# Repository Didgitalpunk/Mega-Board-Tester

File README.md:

# Mega-Board-Tester
## An I/O tester made with arduino Uno and arduino mega pinout-compatible boards in mind.
A simple and intuitive microcontroller tester with one LED on each output so you can easiy locate a faulty I/O pin.\
Made for arduino Uno and arduino mega pin-compatible boards (uno, mega, due, leonardo, zero, etc.), but absolutely useable with other boards through jumpers of adapter cables!

https://user-images.githubusercontent.com/29690873/228524618-455ece8d-8ada-4359-9d4d-3bbc245a15be.MOV

## Compatibility
| Board    | State |
|----------|:--:|
| Mega     | 🟢 |
| Leonardo | 🛠️ |
| Uno      | 🟢 |
| Zero     | 🟢 |

## Usage -- using Version 1 board
1. Upload the file MEGA_board_tester__program.ino to your Arduino.
2. Connect the tester to your board.
3. Watch!

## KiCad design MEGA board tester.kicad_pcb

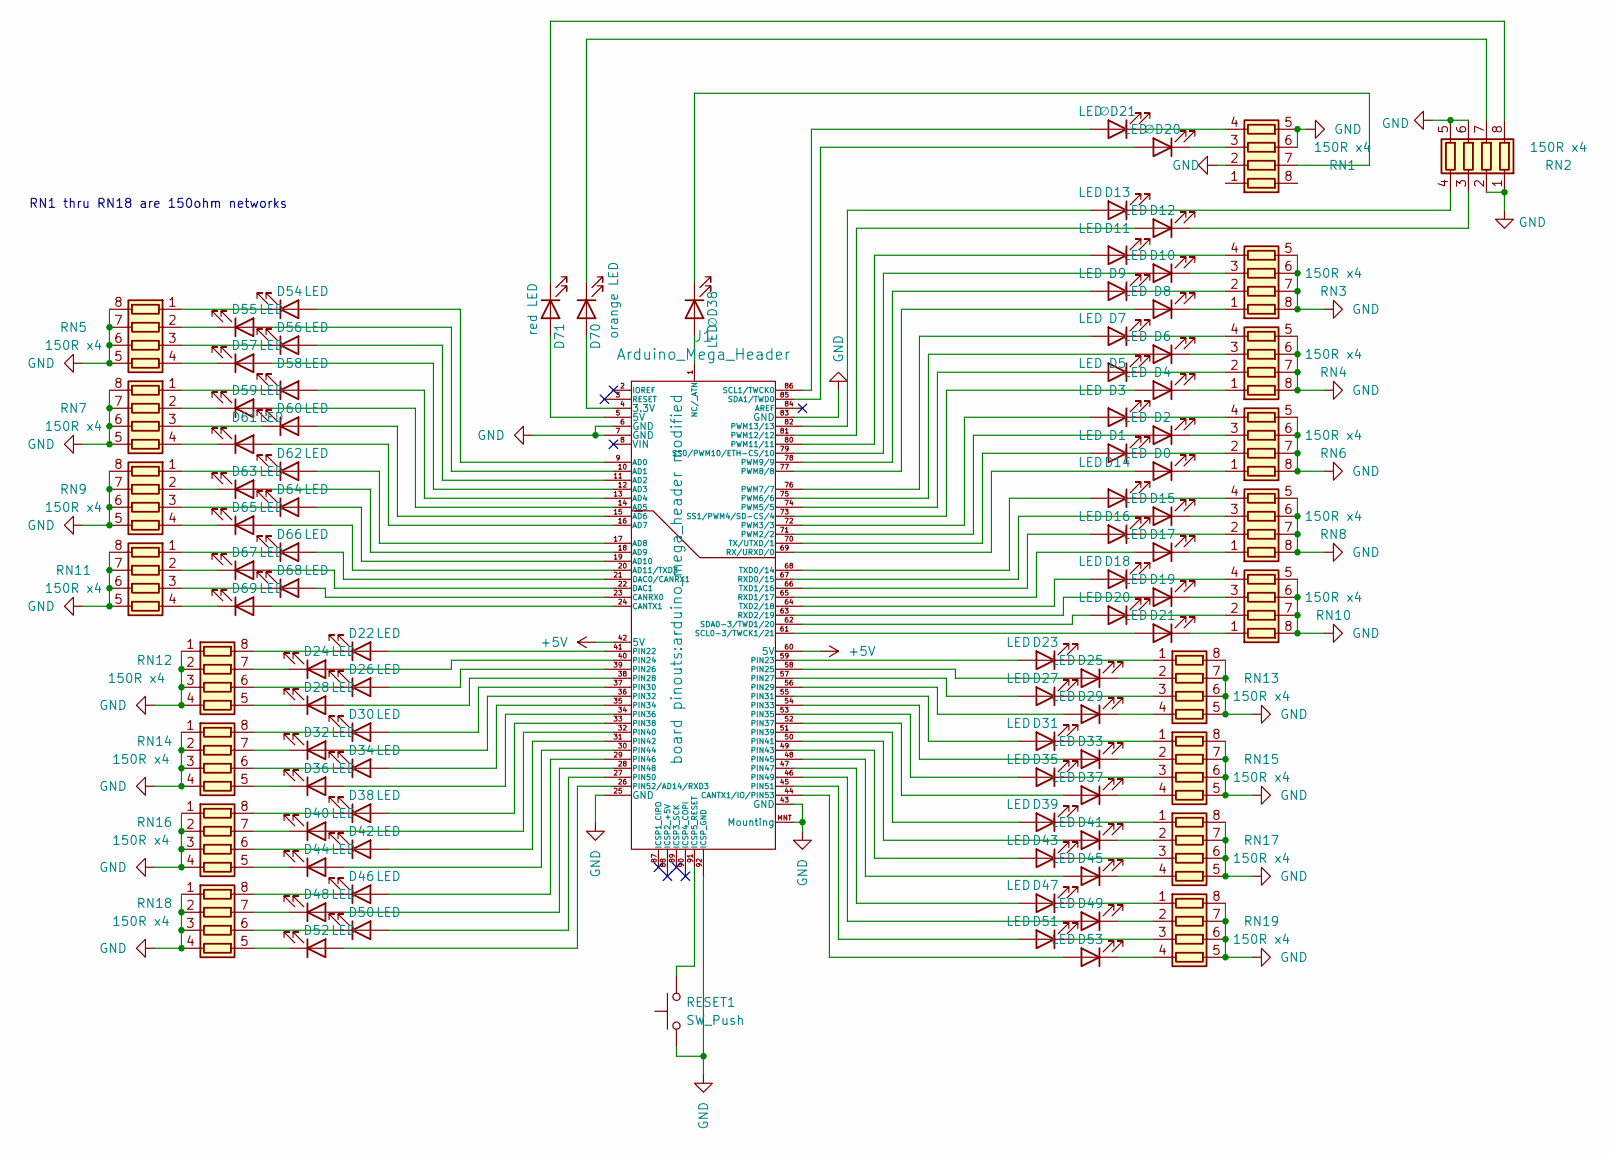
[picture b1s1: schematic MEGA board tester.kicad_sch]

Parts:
D0, D1, D2, D3, D4, D5, D6, D7, D8, D9, D10, D11, D12, D13, D14, D15, D16, D17, D18, D19, D20, D21, D22, D23, D24, D25, D26, D27, D28, D29, D30, D31, D32, D33, D34, D35, D36, D37, D38, D39, D40, D41, D42, D43, D44, D45, D46, D47, D48, D49, D50, D51, D52, D53, D54, D55, D56, D57, D58, D59, D60, D61, D62, D63, D64, D65, D66, D67, D68, D69: LED; D_0805_2012Metric_Pad1.15x1.40mm_HandSolder
D70: orange LED; D_0805_2012Metric_Pad1.15x1.40mm_HandSolder
D71: red LED; D_0805_2012Metric_Pad1.15x1.40mm_HandSolder
J1: Arduino_Mega_Header; arduino_mega_header modified
RESET1: SW_Push; J-lead grayhill switch
RN1, RN2, RN3, RN4, RN5, RN6, RN7, RN8, RN9, RN10, RN11, RN12, RN13, RN14, RN15, RN16, RN17, RN18, RN19: 150R x4; R_Array_convex_EXB-S8Vxxxx
∅D20, ∅D21, ∅D38: LED; D_0805_2012Metric_Pad1.15x1.40mm_HandSolder

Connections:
+5V: J1.42 (5V), J1.60 (5V)
GND: J1.6 (GND), J1.7 (GND), J1.25 (GND), J1.43 (GND), J1.83 (GND), J1.92 (ICSP_GND), J1.MNT (Mounting), RESET1.1, RN1.2 (R2.1), RN1.5 (R4.2), RN1.6 (R3.2), RN2.1 (R1.1), RN2.2 (R2.1), RN2.5 (R4.2), RN2.6 (R3.2), RN3.5 (R4.2), RN3.6 (R3.2), RN3.7 (R2.2), RN3.8 (R1.2), RN4.5 (R4.2), RN4.6 (R3.2), RN4.7 (R2.2), RN4.8 (R1.2), RN5.5 (R4.2), RN5.6 (R3.2), RN5.7 (R2.2), RN5.8 (R1.2), RN6.5 (R4.2), RN6.6 (R3.2), RN6.7 (R2.2), RN6.8 (R1.2), RN7.5 (R4.2), RN7.6 (R3.2), RN7.7 (R2.2), RN7.8 (R1.2), RN8.5 (R4.2), RN8.6 (R3.2), RN8.7 (R2.2), RN8.8 (R1.2), RN9.5 (R4.2), RN9.6 (R3.2), RN9.7 (R2.2), RN9.8 (R1.2), RN10.5 (R4.2), RN10.6 (R3.2), RN10.7 (R2.2), RN10.8 (R1.2), RN11.5 (R4.2), RN11.6 (R3.2), RN11.7 (R2.2), RN11.8 (R1.2), RN12.1 (R1.1), RN12.2 (R2.1), RN12.3 (R3.1), RN12.4 (R4.1), RN13.5 (R4.2), RN13.6 (R3.2), RN13.7 (R2.2), RN13.8 (R1.2), RN14.1 (R1.1), RN14.2 (R2.1), RN14.3 (R3.1), RN14.4 (R4.1), RN15.5 (R4.2), RN15.6 (R3.2), RN15.7 (R2.2), RN15.8 (R1.2), RN16.1 (R1.1), RN16.2 (R2.1), RN16.3 (R3.1), RN16.4 (R4.1), RN17.5 (R4.2), RN17.6 (R3.2), RN17.7 (R2.2), RN17.8 (R1.2), RN18.1 (R1.1), RN18.2 (R2.1), RN18.3 (R3.1), RN18.4 (R4.1), RN19.5 (R4.2), RN19.6 (R3.2), RN19.7 (R2.2), RN19.8 (R1.2); also elsewhere on the board
unnamed: D0.1 (K), RN6.1 (R1.1)
unnamed: D0.2 (A), J1.69 (RX/URXD/0)
unnamed: D1.1 (K), RN6.2 (R2.1)
unnamed: D1.2 (A), J1.70 (TX/UTXD/1)
unnamed: D2.1 (K), RN6.3 (R3.1)
unnamed: D2.2 (A), J1.71 (PWM2/2)
unnamed: D3.1 (K), RN6.4 (R4.1)
unnamed: D3.2 (A), J1.72 (PWM3/3)
unnamed: D4.1 (K), RN4.1 (R1.1)
unnamed: D4.2 (A), J1.73 (SS1/PWM4/SD-CS/4)
unnamed: D5.1 (K), RN4.2 (R2.1)
unnamed: D5.2 (A), J1.74 (PWM5/5)
unnamed: D6.1 (K), RN4.3 (R3.1)
unnamed: D6.2 (A), J1.75 (PWM6/6)
unnamed: D7.1 (K), RN4.4 (R4.1)
unnamed: D7.2 (A), J1.76 (PWM7/7)
unnamed: D8.1 (K), RN3.1 (R1.1)
unnamed: D8.2 (A), J1.77 (PWM8/8)
unnamed: D9.1 (K), RN3.2 (R2.1)
unnamed: D9.2 (A), J1.78 (PWM9/9)
unnamed: D10.1 (K), RN3.3 (R3.1)
unnamed: D10.2 (A), J1.79 (SS0/PWM10/ETH-CS/10)
unnamed: D11.1 (K), RN3.4 (R4.1)
unnamed: D11.2 (A), J1.80 (PWM11/11)
unnamed: D12.1 (K), RN2.3 (R3.1)
unnamed: D12.2 (A), J1.81 (PWM12/12)
unnamed: D13.1 (K), RN2.4 (R4.1)
unnamed: D13.2 (A), J1.82 (PWM13/13)
unnamed: D14.1 (K), RN8.4 (R4.1)
unnamed: D14.2 (A), J1.68 (TXD0/14)
unnamed: D15.1 (K), RN8.3 (R3.1)
unnamed: D15.2 (A), J1.67 (RXD0/15)
unnamed: D16.1 (K), RN8.2 (R2.1)
unnamed: D16.2 (A), J1.66 (TXD1/16)
unnamed: D17.1 (K), RN8.1 (R1.1)
unnamed: D17.2 (A), J1.65 (RXD1/17)
unnamed: D18.1 (K), RN10.4 (R4.1)
unnamed: D18.2 (A), J1.64 (TXD2/18)
unnamed: D19.1 (K), RN10.3 (R3.1)
unnamed: D19.2 (A), J1.63 (RXD2/19)
unnamed: D20.1 (K), RN10.2 (R2.1)
unnamed: D20.2 (A), J1.62 (SDA0-3/TWD1/20)
unnamed: D21.1 (K), RN10.1 (R1.1)
unnamed: D21.2 (A), J1.61 (SCL0-3/TWCK1/21)
unnamed: D22.1 (K), RN12.8 (R1.2)
unnamed: D22.2 (A), J1.41 (PIN22)
unnamed: D23.1 (K), RN13.1 (R1.1)
unnamed: D23.2 (A), J1.59 (PIN23)
unnamed: D24.1 (K), RN12.7 (R2.2)
unnamed: D24.2 (A), J1.40 (PIN24)
unnamed: D25.1 (K), RN13.2 (R2.1)
unnamed: D25.2 (A), J1.58 (PIN25)
unnamed: D26.1 (K), RN12.6 (R3.2)
unnamed: D26.2 (A), J1.39 (PIN26)
unnamed: D27.1 (K), RN13.3 (R3.1)
unnamed: D27.2 (A), J1.57 (PIN27)
unnamed: D28.1 (K), RN12.5 (R4.2)
unnamed: D28.2 (A), J1.38 (PIN28)
unnamed: D29.1 (K), RN13.4 (R4.1)
unnamed: D29.2 (A), J1.56 (PIN29)
unnamed: D30.1 (K), RN14.8 (R1.2)
unnamed: D30.2 (A), J1.37 (PIN30)
unnamed: D31.1 (K), RN15.1 (R1.1)
unnamed: D31.2 (A), J1.55 (PIN31)
unnamed: D32.1 (K), RN14.7 (R2.2)
unnamed: D32.2 (A), J1.36 (PIN32)
unnamed: D33.1 (K), RN15.2 (R2.1)
unnamed: D33.2 (A), J1.54 (PIN33)
unnamed: D34.1 (K), RN14.6 (R3.2)
unnamed: D34.2 (A), J1.35 (PIN34)
unnamed: D35.1 (K), RN15.3 (R3.1)
unnamed: D35.2 (A), J1.53 (PIN35)
unnamed: D36.1 (K), RN14.5 (R4.2)
unnamed: D36.2 (A), J1.34 (PIN36)
unnamed: D37.1 (K), RN15.4 (R4.1)
unnamed: D37.2 (A), J1.52 (PIN37)
unnamed: D38.1 (K), RN16.8 (R1.2)
unnamed: D38.2 (A), J1.33 (PIN38)
unnamed: D39.1 (K), RN17.1 (R1.1)
unnamed: D39.2 (A), J1.51 (PIN39)
unnamed: D40.1 (K), RN16.7 (R2.2)
unnamed: D40.2 (A), J1.32 (PIN40)
unnamed: D41.1 (K), RN17.2 (R2.1)
unnamed: D41.2 (A), J1.50 (PIN41)
unnamed: D42.1 (K), RN16.6 (R3.2)
unnamed: D42.2 (A), J1.31 (PIN42)
unnamed: D43.1 (K), RN17.3 (R3.1)
unnamed: D43.2 (A), J1.49 (PIN43)
unnamed: D44.1 (K), RN16.5 (R4.2)
unnamed: D44.2 (A), J1.30 (PIN44)
unnamed: D45.1 (K), RN17.4 (R4.1)
unnamed: D45.2 (A), J1.48 (PIN45)
unnamed: D46.1 (K), RN18.8 (R1.2)
unnamed: D46.2 (A), J1.29 (PIN46)
unnamed: D47.1 (K), RN19.1 (R1.1)
unnamed: D47.2 (A), J1.47 (PIN47)
unnamed: D48.1 (K), RN18.7 (R2.2)
unnamed: D48.2 (A), J1.28 (PIN48)
unnamed: D49.1 (K), RN19.2 (R2.1)
unnamed: D49.2 (A), J1.46 (PIN49)
unnamed: D50.1 (K), RN18.6 (R3.2)
unnamed: D50.2 (A), J1.27 (PIN50)
unnamed: D51.1 (K), RN19.3 (R3.1)
unnamed: D51.2 (A), J1.45 (PIN51)
unnamed: D52.1 (K), RN18.5 (R4.2)
unnamed: D52.2 (A), J1.26 (PIN52/AD14/RXD3)
unnamed: D53.1 (K), RN19.4 (R4.1)
unnamed: D53.2 (A), J1.44 (CANTX1/IO/PIN53)
unnamed: D54.1 (K), RN5.1 (R1.1)
unnamed: D54.2 (A), J1.9 (AD0)
unnamed: D55.1 (K), RN5.2 (R2.1)
unnamed: D55.2 (A), J1.10 (AD1)
unnamed: D56.1 (K), RN5.3 (R3.1)
unnamed: D56.2 (A), J1.11 (AD2)
unnamed: D57.1 (K), RN5.4 (R4.1)
unnamed: D57.2 (A), J1.12 (AD3)
unnamed: D58.1 (K), RN7.1 (R1.1)
unnamed: D58.2 (A), J1.13 (AD4)
unnamed: D59.1 (K), RN7.2 (R2.1)
unnamed: D59.2 (A), J1.14 (AD5)
unnamed: D60.1 (K), RN7.3 (R3.1)
unnamed: D60.2 (A), J1.15 (AD6)
unnamed: D61.1 (K), RN7.4 (R4.1)
unnamed: D61.2 (A), J1.16 (AD7)
unnamed: D62.1 (K), RN9.1 (R1.1)
unnamed: D62.2 (A), J1.17 (AD8)
unnamed: D63.1 (K), RN9.2 (R2.1)
unnamed: D63.2 (A), J1.18 (AD9)
unnamed: D64.1 (K), RN9.3 (R3.1)
unnamed: D64.2 (A), J1.19 (AD10)
unnamed: D65.1 (K), RN9.4 (R4.1)
unnamed: D65.2 (A), J1.20 (AD11/TXD3)
unnamed: D66.1 (K), RN11.1 (R1.1)
unnamed: D66.2 (A), J1.21 (DAC0/CANRX1)
unnamed: D67.1 (K), RN11.2 (R2.1)
unnamed: D67.2 (A), J1.22 (DAC1)
unnamed: D68.1 (K), RN11.3 (R3.1)
unnamed: D68.2 (A), J1.23 (CANRX0)
unnamed: D69.1 (K), RN11.4 (R4.1)
unnamed: D69.2 (A), J1.24 (CANTX1)
unnamed: D70.1 (K), RN2.7 (R2.2)
unnamed: D70.2 (A), J1.4 (3.3V)
unnamed: D71.1 (K), RN2.8 (R1.2)
unnamed: D71.2 (A), J1.5 (5V)
unnamed: J1.1 (NC/_ATN), ∅D38.2 (A)
unnamed: J1.85 (SDA1/TWD0), ∅D20.2 (A)
unnamed: J1.86 (SCL1/TWCK0), ∅D21.2 (A)
unnamed: J1.91 (ICSP5_RESET), RESET1.2
unnamed: RN1.3 (R3.1), ∅D20.1 (K)
unnamed: RN1.4 (R4.1), ∅D21.1 (K)
unnamed: RN1.7 (R2.2), ∅D38.1 (K)

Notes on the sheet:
RN1 thru RN18 are 150ohm networks

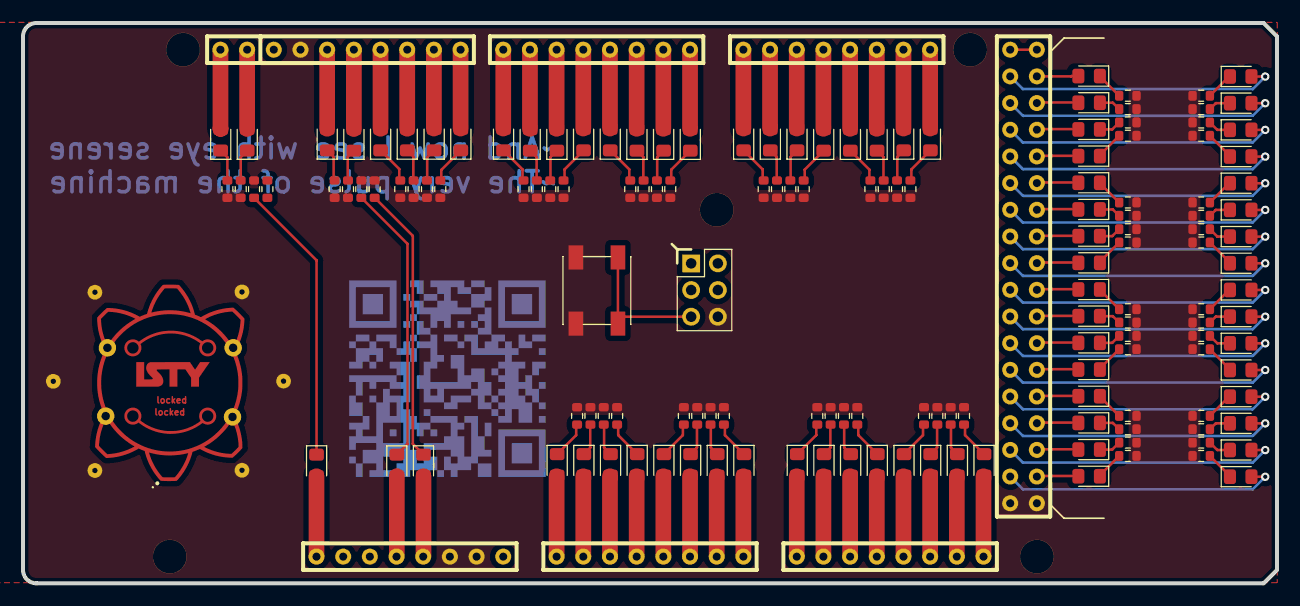
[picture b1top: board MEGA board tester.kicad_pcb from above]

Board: 2 copper layers, 119.4 x 53.3 mm, 97 parts (0 on the bottom side), 153 nets.

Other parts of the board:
Logo1: ISTY LOGO FOR MEGA TEST BOARD 2

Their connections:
GND: Logo1.2; also elsewhere on the board

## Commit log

2023-03-25 Add files via upload
    initial commit:
    - V1 board and layout, boards received and functional after assembly.
    - V1 code, functional.
    - bom folder has the datasheets for the components used on the board
    -all components bought from Mouser (no affiliation) and boards fab'd by PCBway (no affiliation)
2023-03-25 PCB, schematic, and code update
    PCB update:
    - removed the rising sung logo as it was not fab-friendly (was removed by the fab-house from the fab'd PCB)
    - updated version to 1.1
    - added version and date on User.Drawing layer
    - there is a known problem where the data transmission will not happen on arduino if the test board is plugged in, due to pins 0 and 1 (D0 & D1) being used by the board tester. Only (untested) fix fo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
    Schematic:
2023-03-25 derp commit
    saying you're gonna do stuff doesn't make it true until you actually do it.
    Code:
    - did the stuff from the previous commit
2023-03-25 added incrementation
2023-03-25 Renamed folders and files to be navigable easely.
2023-03-25 added diana's beta.cpp file back
2023-03-25 Delete MEGA board tester - testing program directory
    renamed the files and directory.
2023-03-25 fixed array
2023-03-25 Delete MEGA board tester-backups directory
    not needed for the repo.
2023-03-25 cleanup
2023-03-25 added beta.ccp as an arduino program
2023-03-25 removed beta.ino, beta.cpp, and pushed Mega_board_tester__program to V1.2, with board detection! only uno and mega board for now, more will come.
2023-03-26 removed superfluous functions and pointer
2023-03-26 Create beta.ino
    bit of experimental code that doesn't really work any better than the simple increment functions. Might be useful later if we need more features. For now, small size > features.
2023-03-26 messed up formatting
2023-03-27 incremented file version and date due to cleanup.
2023-03-28 deleted beta.ino (it was garbage)
2023-03-28 defines to constexpr
2023-03-28 other defines to constexpr
2023-03-28 PCB updated to version 2 added ∅D20, ∅D21, ∅D38, to ensure compatibility with Arduino Zero boards. (D38 is called ANT on the board, unnamed on mega and unoR3) moved the ISTY logo and credits to make 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
    have yet to decide on what to do with D0 and D1 so they don't interfere with program upload. leave them? remove them and put in test loops for probing? tbd.
2023-03-28 Update MEGA_board_tester_program.ino
    added leonardo (incomplete) and zero to the list.
2023-03-29 Create README.md
    Thanks to @normanalie for the reminder to create a readme, and creating one
2023-03-29 updated readme
    updated short description to be a bit more accurate,
    updated long descriptions to talk about other non-pin-compatible boards
    changed usage to reflect current PCB version (version 1)
    Thanks to Normanalie for creating the README !
2023-03-30 Program Version 2 added, Program V 1.2.1 fixed
2023-03-30 File name errors corrected
2023-03-30 Update board_tester_v2.ino
    updated postfix operators to be in line with standard practice
2023-04-05 Update board_tester_v2.ino
    fixed + and - operators to perform arithmetic without modifying the object. To actually modify the object, call the += or -= operators.
2023-04-05 Update board_tester_v2.ino
    forgot an = sign
2023-04-20 Create TODO.txt
    created TODO file for the next steps in board amelioration.
